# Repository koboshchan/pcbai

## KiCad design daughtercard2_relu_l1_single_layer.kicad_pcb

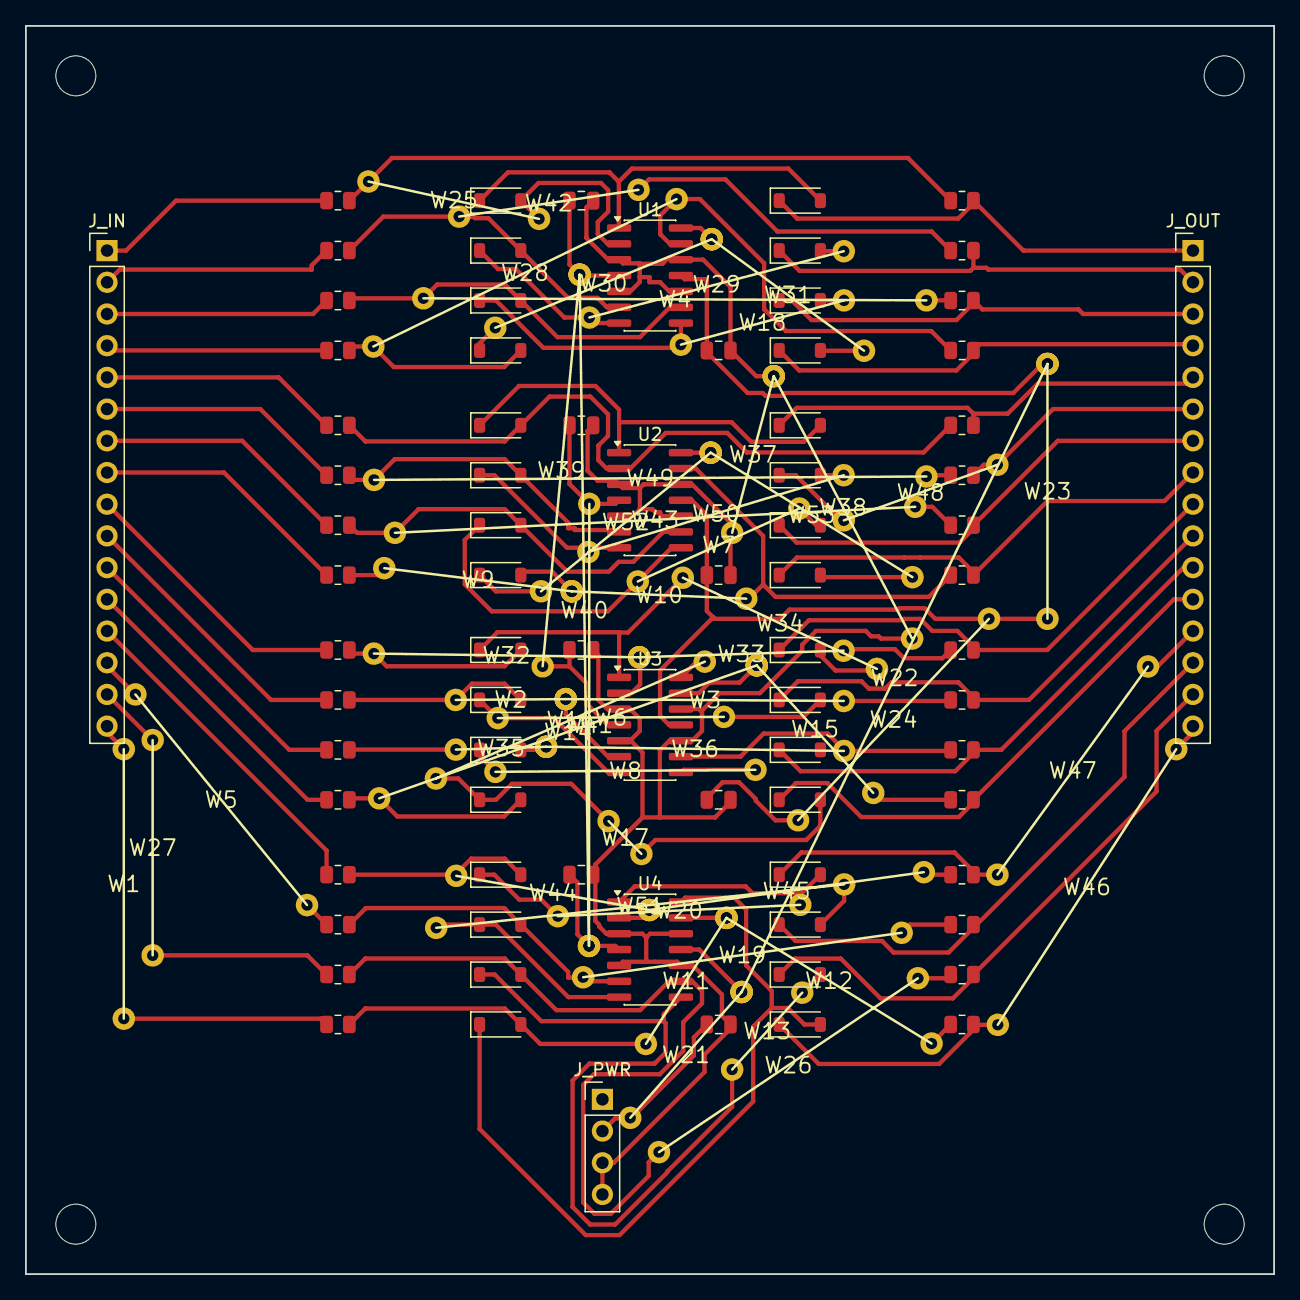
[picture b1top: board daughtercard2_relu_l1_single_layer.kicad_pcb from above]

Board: 2 copper layers, 100.0 x 100.0 mm, 136 parts (0 on the bottom side), 67 nets.

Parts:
C_1_NEG, C_1_POS, C_2_NEG, C_2_POS, C_3_NEG, C_3_POS, C_4_NEG, C_4_POS: 100n; C_0805_2012Metric
D_FB_0, D_FB_1, D_FB_2, D_FB_3, D_FB_4, D_FB_5, D_FB_6, D_FB_7, D_FB_8, D_FB_9, D_FB_10, D_FB_11, D_FB_12, D_FB_13, D_FB_14, D_FB_15: 1N4148; D_SOD-123
D_OUT_0, D_OUT_1, D_OUT_2, D_OUT_3, D_OUT_4, D_OUT_5, D_OUT_6, D_OUT_7, D_OUT_8, D_OUT_9, D_OUT_10, D_OUT_11, D_OUT_12, D_OUT_13, D_OUT_14, D_OUT_15: 1N4148; D_SOD-123
J_IN: V_SUM_IN; PinHeader_1x16_P2.54mm_Vertical
J_OUT: ACT_OUT; PinHeader_1x16_P2.54mm_Vertical
J_PWR: POWER; PinHeader_1x04_P2.54mm_Vertical
MH1, MH2, MH3, MH4: MountingHole_3.2mm_M3
R_FB_0, R_FB_1, R_FB_2, R_FB_3, R_FB_4, R_FB_5, R_FB_6, R_FB_7, R_FB_8, R_FB_9, R_FB_10, R_FB_11, R_FB_12, R_FB_13, R_FB_14, R_FB_15: 10k; R_0805_2012Metric
R_IN_0, R_IN_1, R_IN_2, R_IN_3, R_IN_4, R_IN_5, R_IN_6, R_IN_7, R_IN_8, R_IN_9, R_IN_10, R_IN_11, R_IN_12, R_IN_13, R_IN_14, R_IN_15: 10k; R_0805_2012Metric
U1, U2, U3, U4: TL074; SOIC-14_3.9x8.7mm_P1.27mm
W1, W2, W3, W4, W5, W6, W7, W8, W9, W10, W11, W12, W13, W14, W15, W16, W17, W18, W19, W20, W21, W22, W23, W24, W25, W26, W27, W28, W29, W30, W31, W32, W33, W34, W35, W36, W37, W38, W39, W40, W41, W42, W43, W44, W45, W46, W47, W48, W49, W50, W51, W52, W53: JUMPER; Jumper_Wire

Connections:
+12V: C_1_POS.1, C_2_POS.1, C_3_POS.1, C_4_POS.1, J_PWR.1, U1.4, U2.4, U3.4, U4.4, W39.1, W39.2, W40.1, W40.2, W41.1, W41.2
-12V: C_1_NEG.1, C_2_NEG.1, C_3_NEG.1, C_4_NEG.1, J_PWR.2, U1.11, U2.11, U3.11, U4.11, W21.1, W21.2, W22.1, W22.2, W23.1, W23.2, W24.1, W24.2
ACT_0: D_OUT_0.1, J_OUT.1, R_FB_0.2
ACT_1: D_OUT_1.1, J_OUT.2, R_FB_1.2
ACT_2: D_OUT_2.1, J_OUT.3, R_FB_2.2
ACT_3: D_OUT_3.1, J_OUT.4, R_FB_3.2
ACT_4: D_OUT_4.1, J_OUT.5, R_FB_4.2
ACT_5: D_OUT_5.1, J_OUT.6, R_FB_5.2, W48.1, W48.2
ACT_6: D_OUT_6.1, J_OUT.7, R_FB_6.2
ACT_7: D_OUT_7.1, J_OUT.8, R_FB_7.2
ACT_8: D_OUT_8.1, J_OUT.9, R_FB_8.2
ACT_9: D_OUT_9.1, J_OUT.10, R_FB_9.2
ACT_10: D_OUT_10.1, J_OUT.11, R_FB_10.2
ACT_11: D_OUT_11.1, J_OUT.12, R_FB_11.2
ACT_12: D_OUT_12.1, J_OUT.13, R_FB_12.2, W47.1, W47.2
ACT_13: D_OUT_13.1, J_OUT.14, R_FB_13.2
ACT_14: D_OUT_14.1, J_OUT.15, R_FB_14.2
ACT_15: D_OUT_15.1, J_OUT.16, R_FB_15.2, W46.1, W46.2
GND: C_1_NEG.2, C_1_POS.2, C_2_NEG.2, C_2_POS.2, C_3_NEG.2, C_3_POS.2, C_4_NEG.2, C_4_POS.2, J_PWR.3, J_PWR.4, U1.3, U1.5, U1.10, U1.12, U2.3, U2.5, U2.10, U2.12, U3.3, U3.5, U3.10, U3.12, U4.3, U4.5, U4.10, U4.12, W37.1, W37.2, W38.1, W38.2
INV_IN_0: D_FB_0.2, R_FB_0.1, R_IN_0.2, U1.2, W25.1, W25.2
INV_IN_1: D_FB_1.2, R_FB_1.1, R_IN_1.2, U1.6, W42.1, W42.2
INV_IN_2: D_FB_2.2, R_FB_2.1, R_IN_2.2, U1.9, W4.1, W4.2
INV_IN_3: D_FB_3.2, R_FB_3.1, R_IN_3.2, U1.13, W28.1, W28.2
INV_IN_4: D_FB_4.2, R_FB_4.1, R_IN_4.2, U2.2
INV_IN_5: D_FB_5.2, R_FB_5.1, R_IN_5.2, U2.6, W49.1, W49.2
INV_IN_6: D_FB_6.2, R_FB_6.1, R_IN_6.2, U2.9, W43.1, W43.2
INV_IN_7: D_FB_7.2, R_FB_7.1, R_IN_7.2, U2.13, W9.1, W9.2, W10.1, W10.2
INV_IN_8: D_FB_8.2, R_FB_8.1, R_IN_8.2, U3.2, W32.1, W32.2, W33.1, W33.2
INV_IN_9: D_FB_9.2, R_FB_9.1, R_IN_9.2, U3.6, W2.1, W2.2, W3.1, W3.2
INV_IN_10: D_FB_10.2, R_FB_10.1, R_IN_10.2, U3.9, W35.1, W35.2, W36.1, W36.2
INV_IN_11: D_FB_11.2, R_FB_11.1, R_IN_11.2, U3.13, W14.1, W14.2, W15.1, W15.2
INV_IN_12: D_FB_12.2, R_FB_12.1, R_IN_12.2, U4.2, W44.1, W44.2, W45.1, W45.2
INV_IN_13: D_FB_13.2, R_FB_13.1, R_IN_13.2, U4.6, W19.1, W19.2
INV_IN_14: D_FB_14.2, R_FB_14.1, R_IN_14.2, U4.9, W26.1, W26.2
INV_IN_15: D_FB_15.2, R_FB_15.1, R_IN_15.2, U4.13, W11.1, W11.2, W12.1, W12.2
OP_OUT_0: D_FB_0.1, D_OUT_0.2, U1.1
OP_OUT_1: D_FB_1.1, D_OUT_1.2, U1.7, W29.1, W29.2
OP_OUT_2: D_FB_2.1, D_OUT_2.2, U1.8, W18.1, W18.2
OP_OUT_3: D_FB_3.1, D_OUT_3.2, U1.14, W30.1, W30.2, W31.1, W31.2
OP_OUT_4: D_FB_4.1, D_OUT_4.2, U2.1
OP_OUT_5: D_FB_5.1, D_OUT_5.2, U2.7, W50.1, W50.2
OP_OUT_6: D_FB_6.1, D_OUT_6.2, U2.8, W7.1, W7.2
OP_OUT_7: D_FB_7.1, D_OUT_7.2, U2.14, W52.1, W52.2, W53.1, W53.2
OP_OUT_8: D_FB_8.1, D_OUT_8.2, U3.1, W34.1, W34.2
OP_OUT_9: D_FB_9.1, D_OUT_9.2, U3.7, W6.1, W6.2
OP_OUT_10: D_FB_10.1, D_OUT_10.2, U3.8, W8.1, W8.2
OP_OUT_11: D_FB_11.1, D_OUT_11.2, U3.14, W16.1, W16.2, W17.1, W17.2
OP_OUT_12: D_FB_12.1, D_OUT_12.2, U4.1, W20.1, W20.2
OP_OUT_13: D_FB_13.1, D_OUT_13.2, U4.7, W51.1, W51.2
OP_OUT_14: D_FB_14.1, D_OUT_14.2, U4.8, W13.1, W13.2
OP_OUT_15: D_FB_15.1, D_OUT_15.2, U4.14
V_SUM_0: J_IN.1, R_IN_0.1
V_SUM_1: J_IN.2, R_IN_1.1
V_SUM_2: J_IN.3, R_IN_2.1
V_SUM_3: J_IN.4, R_IN_3.1
V_SUM_4: J_IN.5, R_IN_4.1
V_SUM_5: J_IN.6, R_IN_5.1
V_SUM_6: J_IN.7, R_IN_6.1
V_SUM_7: J_IN.8, R_IN_7.1
V_SUM_8: J_IN.9, R_IN_8.1
V_SUM_9: J_IN.10, R_IN_9.1
V_SUM_10: J_IN.11, R_IN_10.1
V_SUM_11: J_IN.12, R_IN_11.1
V_SUM_12: J_IN.13, R_IN_12.1
V_SUM_13: J_IN.14, R_IN_13.1, W5.1, W5.2
V_SUM_14: J_IN.15, R_IN_14.1, W27.1, W27.2
V_SUM_15: J_IN.16, R_IN_15.1, W1.1, W1.2

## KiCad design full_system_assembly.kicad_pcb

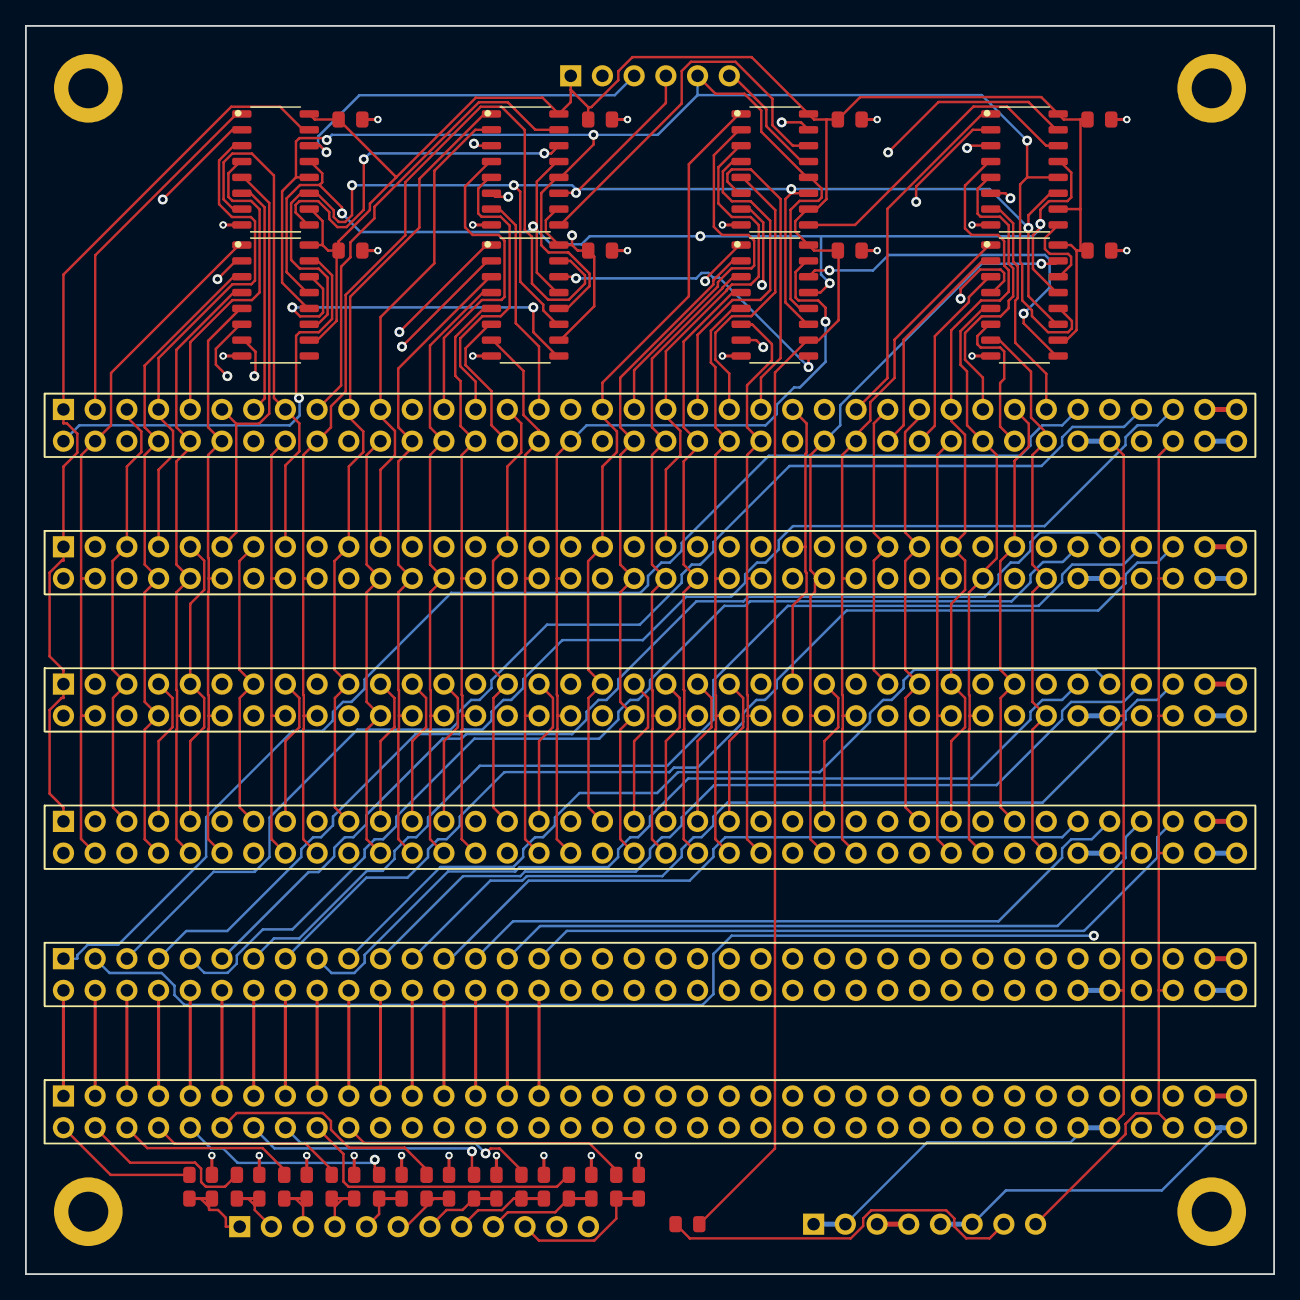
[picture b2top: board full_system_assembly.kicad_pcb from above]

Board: 4 copper layers, 100.0 x 100.0 mm, 50 parts (0 on the bottom side), 133 nets.

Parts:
C_SR1, C_SR2, C_SR3, C_SR4, C_SR5, C_SR6, C_SR7, C_SR8: 0.1uF; C_0805_2012Metric
H1, H2, H3, H4: MountingHole; MountingHole_3.2mm_M3_Pad
J_MCU_SCORES: Scores_DIV_3V3_Out; PinHeader_1x12_P2.54mm_Vertical
J_MCU_SPI: MCU_SPI_In; PinHeader_1x06_P2.54mm_Vertical
J_PWR_IN: Main_Power_In; PinHeader_1x08_P2.54mm_Vertical
J_SLOT0: Slot0: DC1A (L1 Neurons 0..3); PinSocket_2x38_P2.54mm_Vertical
J_SLOT1: Slot1: DC1B (L1 Neurons 4..7); PinSocket_2x38_P2.54mm_Vertical
J_SLOT2: Slot2: DC1C (L1 Neurons 8..11); PinSocket_2x38_P2.54mm_Vertical
J_SLOT3: Slot3: DC1D (L1 Neurons 12..15); PinSocket_2x38_P2.54mm_Vertical
J_SLOT4: Slot4: DC2 (16x Active Precision ReLU); PinSocket_2x38_P2.54mm_Vertical
J_SLOT5: Slot5: DC3 (L2 Weights + 10-Way WTA); PinSocket_2x38_P2.54mm_Vertical
R_BOT_0, R_BOT_1, R_BOT_2, R_BOT_3, R_BOT_4, R_BOT_5, R_BOT_6, R_BOT_7, R_BOT_8, R_BOT_9: 20k; R_0805_2012Metric
R_PWR5: 0R; R_0805_2012Metric
R_TOP_0, R_TOP_1, R_TOP_2, R_TOP_3, R_TOP_4, R_TOP_5, R_TOP_6, R_TOP_7, R_TOP_8, R_TOP_9: 10k; R_0805_2012Metric
U_SR1, U_SR2, U_SR3, U_SR4, U_SR5, U_SR6, U_SR7, U_SR8: 74HC595D; SOIC-16_3.9x9.9mm_P1.27mm

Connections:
+5V: C_SR1.1, C_SR2.1, C_SR3.1, C_SR4.1, C_SR5.1, C_SR6.1, C_SR7.1, C_SR8.1, J_MCU_SPI.1, R_PWR5.2, U_SR1.10, U_SR1.16, U_SR2.10, U_SR2.16, U_SR3.10, U_SR3.16, U_SR4.10, U_SR4.16, U_SR5.10, U_SR5.16, U_SR6.10, U_SR6.16, U_SR7.10, U_SR7.16, U_SR8.10, U_SR8.16
+5V_REF: J_PWR_IN.7, J_SLOT0.B35, J_SLOT1.B35, J_SLOT2.B35, J_SLOT3.B35, J_SLOT4.B35, J_SLOT5.B35, R_PWR5.1
+12V: J_PWR_IN.1, J_PWR_IN.2, J_SLOT0.B33, J_SLOT0.B34, J_SLOT1.B33, J_SLOT1.B34, J_SLOT2.B33, J_SLOT2.B34, J_SLOT3.B33, J_SLOT3.B34, J_SLOT4.B33, J_SLOT4.B34, J_SLOT5.B33, J_SLOT5.B34
-5V_REF: J_PWR_IN.8, J_SLOT0.B36, J_SLOT1.B36, J_SLOT2.B36, J_SLOT3.B36, J_SLOT4.B36, J_SLOT5.B36
-12V: J_PWR_IN.5, J_PWR_IN.6, J_SLOT0.B37, J_SLOT0.B38, J_SLOT1.B37, J_SLOT1.B38, J_SLOT2.B37, J_SLOT2.B38, J_SLOT3.B37, J_SLOT3.B38, J_SLOT4.B37, J_SLOT4.B38, J_SLOT5.B37, J_SLOT5.B38
ACT_0: J_SLOT4.B1, J_SLOT5.A1
ACT_1: J_SLOT4.B2, J_SLOT5.A2
ACT_2: J_SLOT4.B3, J_SLOT5.A3
ACT_3: J_SLOT4.B4, J_SLOT5.A4
ACT_4: J_SLOT4.B5, J_SLOT5.A5
ACT_5: J_SLOT4.B6, J_SLOT5.A6
ACT_6: J_SLOT4.B7, J_SLOT5.A7
ACT_7: J_SLOT4.B8, J_SLOT5.A8
ACT_8: J_SLOT4.B9, J_SLOT5.A9
ACT_9: J_SLOT4.B10, J_SLOT5.A10
ACT_10: J_SLOT4.B11, J_SLOT5.A11
ACT_11: J_SLOT4.B12, J_SLOT5.A12
ACT_12: J_SLOT4.B13, J_SLOT5.A13
ACT_13: J_SLOT4.B14, J_SLOT5.A14
ACT_14: J_SLOT4.B15, J_SLOT5.A15
ACT_15: J_SLOT4.B16, J_SLOT5.A16
GND: C_SR1.2, C_SR2.2, C_SR3.2, C_SR4.2, C_SR5.2, C_SR6.2, C_SR7.2, C_SR8.2, H1.1, H2.1, H3.1, H4.1, J_MCU_SCORES.11, J_MCU_SCORES.12, J_MCU_SPI.2, J_PWR_IN.3, J_PWR_IN.4, J_SLOT0.A37, J_SLOT0.A38, J_SLOT1.A37, J_SLOT1.A38, J_SLOT2.A37, J_SLOT2.A38, J_SLOT3.A37, J_SLOT3.A38, J_SLOT4.A17, J_SLOT4.A18, J_SLOT4.A19, J_SLOT4.A20, J_SLOT4.A21, J_SLOT4.A22, J_SLOT4.A23, J_SLOT4.A24, J_SLOT4.A25, J_SLOT4.A26, J_SLOT4.A27, J_SLOT4.A28, J_SLOT4.A29, J_SLOT4.A30, J_SLOT4.A31, J_SLOT4.A32, J_SLOT4.A33, J_SLOT4.A34, J_SLOT4.A35, J_SLOT4.A36, J_SLOT4.A37, J_SLOT4.A38, J_SLOT4.B17, J_SLOT4.B18, J_SLOT4.B19, J_SLOT4.B20, J_SLOT4.B21, J_SLOT4.B22, J_SLOT4.B23, J_SLOT4.B24, J_SLOT4.B25, J_SLOT4.B26, J_SLOT4.B27, J_SLOT4.B28, J_SLOT4.B29, J_SLOT4.B30, J_SLOT4.B31, J_SLOT4.B32, J_SLOT5.A17, J_SLOT5.A18, J_SLOT5.A19, J_SLOT5.A20, J_SLOT5.A21, J_SLOT5.A22, J_SLOT5.A23, J_SLOT5.A24, J_SLOT5.A25, J_SLOT5.A26, J_SLOT5.A27, J_SLOT5.A28, J_SLOT5.A29, J_SLOT5.A30, J_SLOT5.A31, J_SLOT5.A32, J_SLOT5.A33, J_SLOT5.A34, J_SLOT5.A35, J_SLOT5.A36, J_SLOT5.A37, J_SLOT5.A38, J_SLOT5.B11, J_SLOT5.B12, J_SLOT5.B13, J_SLOT5.B14, J_SLOT5.B15, J_SLOT5.B16, J_SLOT5.B17, J_SLOT5.B18, J_SLOT5.B19, J_SLOT5.B20, J_SLOT5.B21, J_SLOT5.B22, J_SLOT5.B23, J_SLOT5.B24, J_SLOT5.B25, J_SLOT5.B26, J_SLOT5.B27, J_SLOT5.B28, J_SLOT5.B29, J_SLOT5.B30, J_SLOT5.B31, J_SLOT5.B32, R_BOT_0.1, R_BOT_1.1, R_BOT_2.1, R_BOT_3.1, R_BOT_4.1, R_BOT_5.1, R_BOT_6.1, R_BOT_7.1, R_BOT_8.1, R_BOT_9.1, U_SR1.8, U_SR2.8, U_SR3.8, U_SR4.8, U_SR5.8, U_SR6.8, U_SR7.8, U_SR8.8
IN_0: J_SLOT0.A1, J_SLOT1.A1, J_SLOT2.A1, J_SLOT3.A1, U_SR1.15
IN_1: J_SLOT0.A2, J_SLOT1.A2, J_SLOT2.A2, J_SLOT3.A2, U_SR1.1
IN_2: J_SLOT0.A3, J_SLOT1.A3, J_SLOT2.A3, J_SLOT3.A3, U_SR1.2
IN_3: J_SLOT0.A4, J_SLOT1.A4, J_SLOT2.A4, J_SLOT3.A4, U_SR1.3
IN_4: J_SLOT0.A5, J_SLOT1.A5, J_SLOT2.A5, J_SLOT3.A5, U_SR1.4
IN_5: J_SLOT0.A6, J_SLOT1.A6, J_SLOT2.A6, J_SLOT3.A6, U_SR1.5
IN_6: J_SLOT0.A7, J_SLOT1.A7, J_SLOT2.A7, J_SLOT3.A7, U_SR1.6
IN_7: J_SLOT0.A8, J_SLOT1.A8, J_SLOT2.A8, J_SLOT3.A8, U_SR1.7
IN_8: J_SLOT0.A9, J_SLOT1.A9, J_SLOT2.A9, J_SLOT3.A9, U_SR2.15
IN_9: J_SLOT0.A10, J_SLOT1.A10, J_SLOT2.A10, J_SLOT3.A10, U_SR2.1
IN_10: J_SLOT0.A11, J_SLOT1.A11, J_SLOT2.A11, J_SLOT3.A11, U_SR2.2
IN_11: J_SLOT0.A12, J_SLOT1.A12, J_SLOT2.A12, J_SLOT3.A12, U_SR2.3
IN_12: J_SLOT0.A13, J_SLOT1.A13, J_SLOT2.A13, J_SLOT3.A13, U_SR2.4
IN_13: J_SLOT0.A14, J_SLOT1.A14, J_SLOT2.A14, J_SLOT3.A14, U_SR2.5
IN_14: J_SLOT0.A15, J_SLOT1.A15, J_SLOT2.A15, J_SLOT3.A15, U_SR2.6
IN_15: J_SLOT0.A16, J_SLOT1.A16, J_SLOT2.A16, J_SLOT3.A16, U_SR2.7
IN_16: J_SLOT0.A17, J_SLOT1.A17, J_SLOT2.A17, J_SLOT3.A17, U_SR3.15
IN_17: J_SLOT0.A18, J_SLOT1.A18, J_SLOT2.A18, J_SLOT3.A18, U_SR3.1
IN_18: J_SLOT0.A19, J_SLOT1.A19, J_SLOT2.A19, J_SLOT3.A19, U_SR3.2
IN_19: J_SLOT0.A20, J_SLOT1.A20, J_SLOT2.A20, J_SLOT3.A20, U_SR3.3
IN_20: J_SLOT0.A21, J_SLOT1.A21, J_SLOT2.A21, J_SLOT3.A21, U_SR3.4
IN_21: J_SLOT0.A22, J_SLOT1.A22, J_SLOT2.A22, J_SLOT3.A22, U_SR3.5
IN_22: J_SLOT0.A23, J_SLOT1.A23, J_SLOT2.A23, J_SLOT3.A23, U_SR3.6
IN_23: J_SLOT0.A24, J_SLOT1.A24, J_SLOT2.A24, J_SLOT3.A24, U_SR3.7
IN_24: J_SLOT0.A25, J_SLOT1.A25, J_SLOT2.A25, J_SLOT3.A25, U_SR4.15
IN_25: J_SLOT0.A26, J_SLOT1.A26, J_SLOT2.A26, J_SLOT3.A26, U_SR4.1
IN_26: J_SLOT0.A27, J_SLOT1.A27, J_SLOT2.A27, J_SLOT3.A27, U_SR4.2
IN_27: J_SLOT0.A28, J_SLOT1.A28, J_SLOT2.A28, J_SLOT3.A28, U_SR4.3
IN_28: J_SLOT0.A29, J_SLOT1.A29, J_SLOT2.A29, J_SLOT3.A29, U_SR4.4
IN_29: J_SLOT0.A30, J_SLOT1.A30, J_SLOT2.A30, J_SLOT3.A30, U_SR4.5
IN_30: J_SLOT0.A31, J_SLOT1.A31, J_SLOT2.A31, J_SLOT3.A31, U_SR4.6
IN_31: J_SLOT0.A32, J_SLOT1.A32, J_SLOT2.A32, J_SLOT3.A32, U_SR4.7
IN_32: J_SLOT0.B1, J_SLOT1.B1, J_SLOT2.B1, J_SLOT3.B1, U_SR8.15
IN_33: J_SLOT0.B2, J_SLOT1.B2, J_SLOT2.B2, J_SLOT3.B2, U_SR8.1
IN_34: J_SLOT0.B3, J_SLOT1.B3, J_SLOT2.B3, J_SLOT3.B3, U_SR8.2
IN_35: J_SLOT0.B4, J_SLOT1.B4, J_SLOT2.B4, J_SLOT3.B4, U_SR8.3
IN_36: J_SLOT0.B5, J_SLOT1.B5, J_SLOT2.B5, J_SLOT3.B5, U_SR8.4
IN_37: J_SLOT0.B6, J_SLOT1.B6, J_SLOT2.B6, J_SLOT3.B6, U_SR8.5
IN_38: J_SLOT0.B7, J_SLOT1.B7, J_SLOT2.B7, J_SLOT3.B7, U_SR8.6
IN_39: J_SLOT0.B8, J_SLOT1.B8, J_SLOT2.B8, J_SLOT3.B8, U_SR8.7
IN_40: J_SLOT0.B9, J_SLOT1.B9, J_SLOT2.B9, J_SLOT3.B9, U_SR7.15
IN_41: J_SLOT0.B10, J_SLOT1.B10, J_SLOT2.B10, J_SLOT3.B10, U_SR7.1
IN_42: J_SLOT0.B11, J_SLOT1.B11, J_SLOT2.B11, J_SLOT3.B11, U_SR7.2
IN_43: J_SLOT0.B12, J_SLOT1.B12, J_SLOT2.B12, J_SLOT3.B12, U_SR7.3
IN_44: J_SLOT0.B13, J_SLOT1.B13, J_SLOT2.B13, J_SLOT3.B13, U_SR7.4
IN_45: J_SLOT0.B14, J_SLOT1.B14, J_SLOT2.B14, J_SLOT3.B14, U_SR7.5
IN_46: J_SLOT0.B15, J_SLOT1.B15, J_SLOT2.B15, J_SLOT3.B15, U_SR7.6
IN_47: J_SLOT0.B16, J_SLOT1.B16, J_SLOT2.B16, J_SLOT3.B16, U_SR7.7
IN_48: J_SLOT0.B17, J_SLOT1.B17, J_SLOT2.B17, J_SLOT3.B17, U_SR6.15
IN_49: J_SLOT0.B18, J_SLOT1.B18, J_SLOT2.B18, J_SLOT3.B18, U_SR6.1
IN_50: J_SLOT0.B19, J_SLOT1.B19, J_SLOT2.B19, J_SLOT3.B19, U_SR6.2
IN_51: J_SLOT0.B20, J_SLOT1.B20, J_SLOT2.B20, J_SLOT3.B20, U_SR6.3
IN_52: J_SLOT0.B21, J_SLOT1.B21, J_SLOT2.B21, J_SLOT3.B21, U_SR6.4
IN_53: J_SLOT0.B22, J_SLOT1.B22, J_SLOT2.B22, J_SLOT3.B22, U_SR6.5
IN_54: J_SLOT0.B23, J_SLOT1.B23, J_SLOT2.B23, J_SLOT3.B23, U_SR6.6
IN_55: J_SLOT0.B24, J_SLOT1.B24, J_SLOT2.B24, J_SLOT3.B24, U_SR6.7
IN_56: J_SLOT0.B25, J_SLOT1.B25, J_SLOT2.B25, J_SLOT3.B25, U_SR5.15
IN_57: J_SLOT0.B26, J_SLOT1.B26, J_SLOT2.B26, J_SLOT3.B26, U_SR5.1
IN_58: J_SLOT0.B27, J_SLOT1.B27, J_SLOT2.B27, J_SLOT3.B27, U_SR5.2
IN_59: J_SLOT0.B28, J_SLOT1.B28, J_SLOT2.B28, J_SLOT3.B28, U_SR5.3
IN_60: J_SLOT0.B29, J_SLOT1.B29, J_SLOT2.B29, J_SLOT3.B29, U_SR5.4
IN_61: J_SLOT0.B30, J_SLOT1.B30, J_SLOT2.B30, J_SLOT3.B30, U_SR5.5
IN_62: J_SLOT0.B31, J_SLOT1.B31, J_SLOT2.B31, J_SLOT3.B31, U_SR5.6
IN_63: J_SLOT0.B32, J_SLOT1.B32, J_SLOT2.B32, J_SLOT3.B32, U_SR5.7
SCORE_0: J_SLOT5.B1, R_TOP_0.1
SCORE_1: J_SLOT5.B2, R_TOP_1.1
SCORE_2: J_SLOT5.B3, R_TOP_2.1
SCORE_3: J_SLOT5.B4, R_TOP_3.1
SCORE_4: J_SLOT5.B5, R_TOP_4.1
SCORE_5: J_SLOT5.B6, R_TOP_5.1
SCORE_6: J_SLOT5.B7, R_TOP_6.1
SCORE_7: J_SLOT5.B8, R_TOP_7.1
SCORE_8: J_SLOT5.B9, R_TOP_8.1
SCORE_9: J_SLOT5.B10, R_TOP_9.1
SCORE_DIV_0: J_MCU_SCORES.1, R_BOT_0.2, R_TOP_0.2
SCORE_DIV_1: J_MCU_SCORES.2, R_BOT_1.2, R_TOP_1.2
SCORE_DIV_2: J_MCU_SCORES.3, R_BOT_2.2, R_TOP_2.2
SCORE_DIV_3: J_MCU_SCORES.4, R_BOT_3.2, R_TOP_3.2
SCORE_DIV_4: J_MCU_SCORES.5, R_BOT_4.2, R_TOP_4.2
SCORE_DIV_5: J_MCU_SCORES.6, R_BOT_5.2, R_TOP_5.2
SCORE_DIV_6: J_MCU_SCORES.7, R_BOT_6.2, R_TOP_6.2
SCORE_DIV_7: J_MCU_SCORES.8, R_BOT_7.2, R_TOP_7.2
SCORE_DIV_8: J_MCU_SCORES.9, R_BOT_8.2, R_TOP_8.2
SCORE_DIV_9: J_MCU_SCORES.10, R_BOT_9.2, R_TOP_9.2
SPI_LATCH: J_MCU_SPI.5, U_SR1.12, U_SR2.12, U_SR3.12, U_SR4.12, U_SR5.12, U_SR6.12, U_SR7.12, U_SR8.12
SPI_MOSI: J_MCU_SPI.3, U_SR1.14
SPI_OE: J_MCU_SPI.6, U_SR1.13, U_SR2.13, U_SR3.13, U_SR4.13, U_SR5.13, U_SR6.13, U_SR7.13, U_SR8.13
SPI_SCK: J_MCU_SPI.4, U_SR1.11, U_SR2.11, U_SR3.11, U_SR4.11, U_SR5.11, U_SR6.11, U_SR7.11, U_SR8.11
SR_CHAIN_1: U_SR1.9, U_SR2.14
SR_CHAIN_2: U_SR2.9, U_SR3.14
SR_CHAIN_3: U_SR3.9, U_SR4.14
SR_CHAIN_4: U_SR4.9, U_SR5.14
SR_CHAIN_5: U_SR5.9, U_SR6.14
SR_CHAIN_6: U_SR6.9, U_SR7.14
SR_CHAIN_7: U_SR7.9, U_SR8.14
V_SUM_0: J_SLOT0.A33, J_SLOT4.A1
V_SUM_1: J_SLOT0.A34, J_SLOT4.A2
V_SUM_2: J_SLOT0.A35, J_SLOT4.A3
V_SUM_3: J_SLOT0.A36, J_SLOT4.A4
V_SUM_4: J_SLOT1.A33, J_SLOT4.A5
V_SUM_5: J_SLOT1.A34, J_SLOT4.A6
V_SUM_6: J_SLOT1.A35, J_SLOT4.A7
V_SUM_7: J_SLOT1.A36, J_SLOT4.A8
V_SUM_8: J_SLOT2.A33, J_SLOT4.A9
V_SUM_9: J_SLOT2.A34, J_SLOT4.A10
V_SUM_10: J_SLOT2.A35, J_SLOT4.A11
V_SUM_11: J_SLOT2.A36, J_SLOT4.A12
V_SUM_12: J_SLOT3.A33, J_SLOT4.A13
V_SUM_13: J_SLOT3.A34, J_SLOT4.A14
V_SUM_14: J_SLOT3.A35, J_SLOT4.A15
V_SUM_15: J_SLOT3.A36, J_SLOT4.A16

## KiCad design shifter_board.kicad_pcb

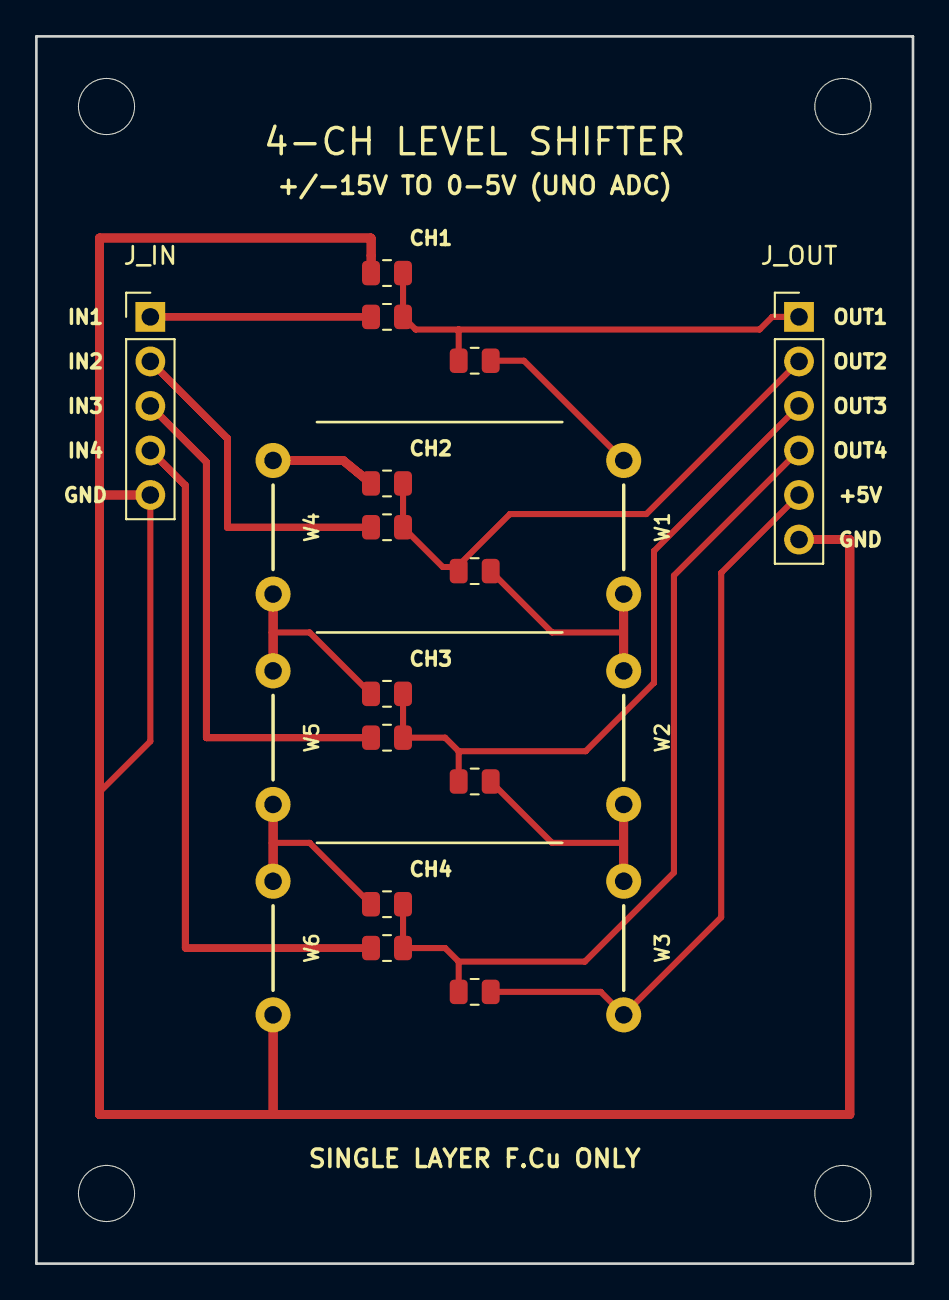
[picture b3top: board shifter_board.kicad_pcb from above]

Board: 2 copper layers, 50.0 x 70.0 mm, 24 parts (0 on the bottom side), 16 nets.

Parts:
J_IN: 1x05_IN_GND; PinHeader_1x05_P2.54mm_Vertical
J_OUT: 1x06_OUT_5V_GND; PinHeader_1x06_P2.54mm_Vertical
MH1, MH2, MH3, MH4: MountingHole_3.2mm_M3
R1_PD, R1_PU, R2_PD, R2_PU, R3_PD, R3_PU, R4_PD, R4_PU: 10k; R_0805_2012Metric
R1_TOP, R2_TOP, R3_TOP, R4_TOP: 33k; R_0805_2012Metric
W1, W2, W3, W4, W5, W6: Jumper_Wire

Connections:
+5V: J_OUT.5, R4_PU.2, W3.2
+5V_CH1: R1_PU.2, W1.1
+5V_CH2: R2_PU.2, W1.2, W2.1
+5V_CH3: R3_PU.2, W2.2, W3.1
GND: J_IN.5, J_OUT.6, R1_PD.1, W6.2
GND_CH1: R2_PD.1, W4.1
GND_CH2: R3_PD.1, W4.2, W5.1
GND_CH3: R4_PD.1, W5.2, W6.1
IN1: J_IN.1, R1_TOP.1
IN2: J_IN.2, R2_TOP.1
IN3: J_IN.3, R3_TOP.1
IN4: J_IN.4, R4_TOP.1
MID1: J_OUT.1, R1_PD.2, R1_PU.1, R1_TOP.2
MID2: J_OUT.2, R2_PD.2, R2_PU.1, R2_TOP.2
MID3: J_OUT.3, R3_PD.2, R3_PU.1, R3_TOP.2
MID4: J_OUT.4, R4_PD.2, R4_PU.1, R4_TOP.2

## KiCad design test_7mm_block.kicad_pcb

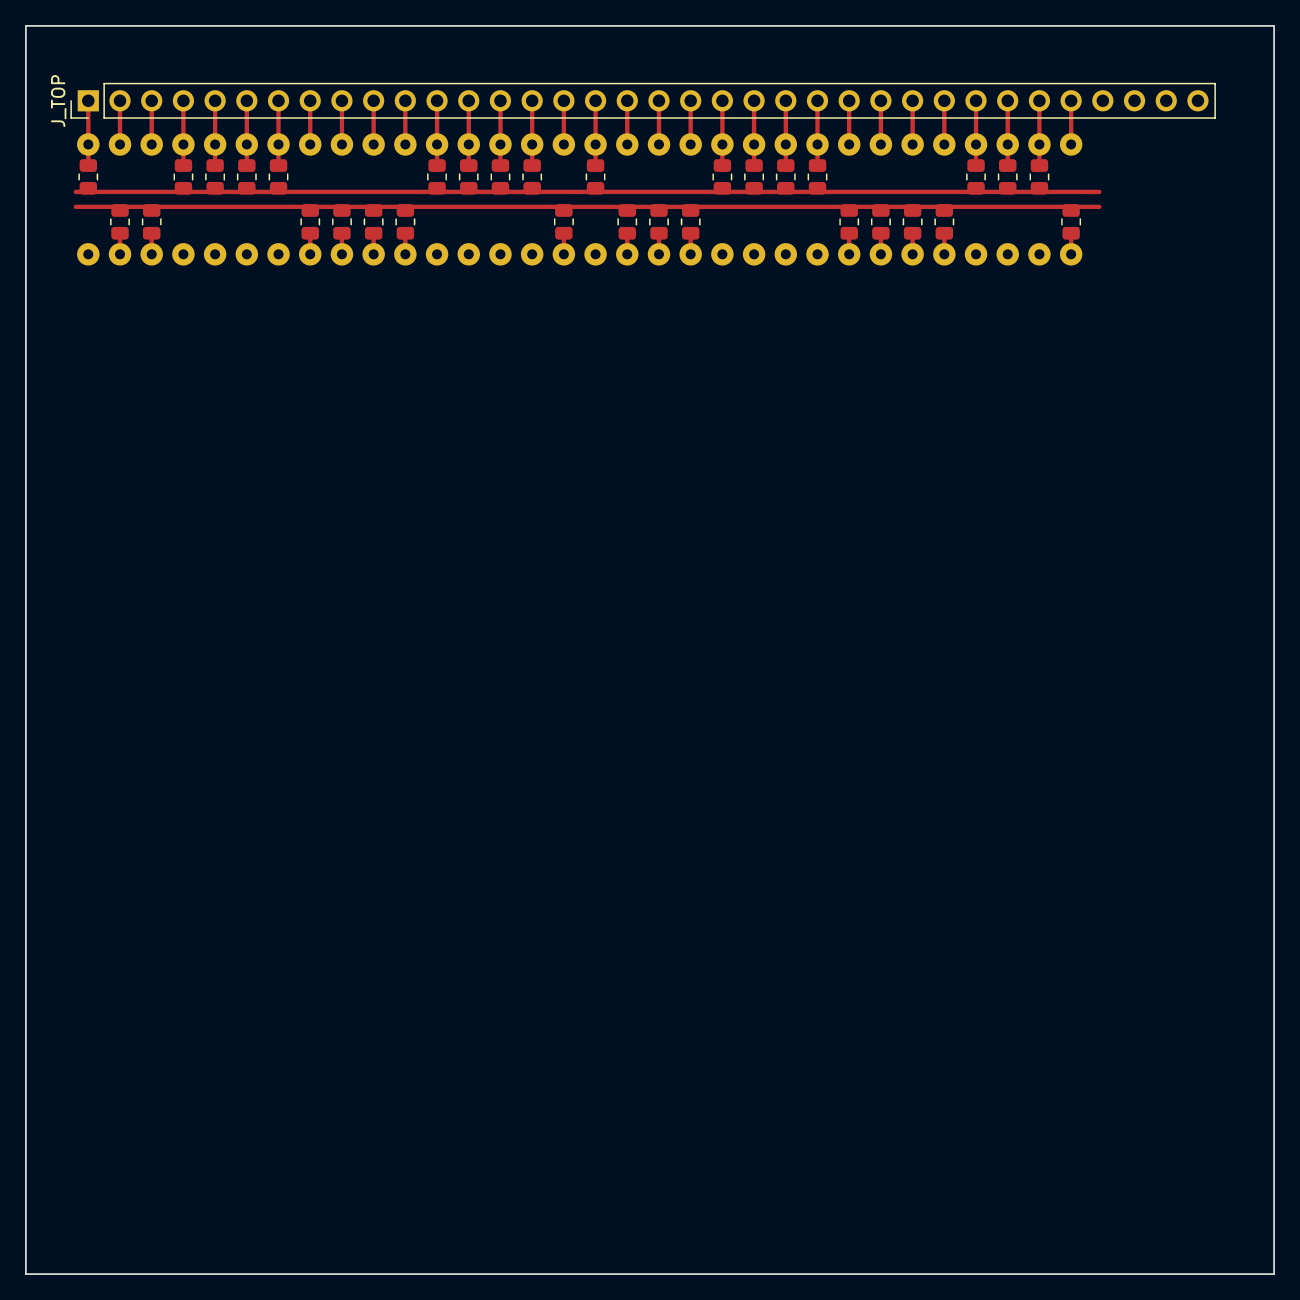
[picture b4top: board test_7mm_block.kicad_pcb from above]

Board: 2 copper layers, 100.0 x 100.0 mm, 65 parts (0 on the bottom side), 34 nets.

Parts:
J_TOP: INPUTS_0_31_PWR; PinHeader_1x36_P2.54mm_Vertical
R1_0_0, R1_4_0, R1_7_0, R1_21_0, R1_22_0, R1_27_0: 12k; R_0805_2012Metric
R1_1_0, R1_10_0, R1_28_0: 200k; R_0805_2012Metric
R1_2_0, R1_8_0, R1_16_0, R1_24_0, R1_29_0: 22k; R_0805_2012Metric
R1_3_0: 100k; R_0805_2012Metric
R1_5_0, R1_9_0, R1_13_0, R1_14_0, R1_25_0, R1_26_0: 33k; R_0805_2012Metric
R1_6_0, R1_11_0, R1_17_0: 75k; R_0805_2012Metric
R1_12_0: 18k; R_0805_2012Metric
R1_15_0: 300k; R_0805_2012Metric
R1_18_0: 43k; R_0805_2012Metric
R1_19_0: 10k; R_0805_2012Metric
R1_20_0: 51k; R_0805_2012Metric
R1_23_0: 15k; R_0805_2012Metric
R1_30_0: 20k; R_0805_2012Metric
R1_31_0: 390k; R_0805_2012Metric
W1, W2, W3, W4, W5, W6, W7, W8, W9, W10, W11, W12, W13, W14, W15, W16, W17, W18, W19, W20, W21, W22, W23, W24, W25, W26, W27, W28, W29, W30, W31, W32: JUMPER; Jumper_Wire

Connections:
IN_0: J_TOP.1, R1_0_0.1, W1.1
IN_1: J_TOP.2, R1_1_0.1, W2.1
IN_2: J_TOP.3, R1_2_0.1, W3.1
IN_3: J_TOP.4, R1_3_0.1, W4.1
IN_4: J_TOP.5, R1_4_0.1, W5.1
IN_5: J_TOP.6, R1_5_0.1, W6.1
IN_6: J_TOP.7, R1_6_0.1, W7.1
IN_7: J_TOP.8, R1_7_0.1, W8.1
IN_8: J_TOP.9, R1_8_0.1, W9.1
IN_9: J_TOP.10, R1_9_0.1, W10.1
IN_10: J_TOP.11, R1_10_0.1, W11.1
IN_11: J_TOP.12, R1_11_0.1, W12.1
IN_12: J_TOP.13, R1_12_0.1, W13.1
IN_13: J_TOP.14, R1_13_0.1, W14.1
IN_14: J_TOP.15, R1_14_0.1, W15.1
IN_15: J_TOP.16, R1_15_0.1, W16.1
IN_16: J_TOP.17, R1_16_0.1, W17.1
IN_17: J_TOP.18, R1_17_0.1, W18.1
IN_18: J_TOP.19, R1_18_0.1, W19.1
IN_19: J_TOP.20, R1_19_0.1, W20.1
IN_20: J_TOP.21, R1_20_0.1, W21.1
IN_21: J_TOP.22, R1_21_0.1, W22.1
IN_22: J_TOP.23, R1_22_0.1, W23.1
IN_23: J_TOP.24, R1_23_0.1, W24.1
IN_24: J_TOP.25, R1_24_0.1, W25.1
IN_25: J_TOP.26, R1_25_0.1, W26.1
IN_26: J_TOP.27, R1_26_0.1, W27.1
IN_27: J_TOP.28, R1_27_0.1, W28.1
IN_28: J_TOP.29, R1_28_0.1, W29.1
IN_29: J_TOP.30, R1_29_0.1, W30.1
IN_30: J_TOP.31, R1_30_0.1, W31.1
IN_31: J_TOP.32, R1_31_0.1, W32.1
SUM_NEG_0: R1_1_0.2, R1_2_0.2, R1_7_0.2, R1_8_0.2, R1_9_0.2, R1_10_0.2, R1_15_0.2, R1_17_0.2, R1_18_0.2, R1_19_0.2, R1_24_0.2, R1_25_0.2, R1_26_0.2, R1_27_0.2, R1_31_0.2
SUM_POS_0: R1_0_0.2, R1_3_0.2, R1_4_0.2, R1_5_0.2, R1_6_0.2, R1_11_0.2, R1_12_0.2, R1_13_0.2, R1_14_0.2, R1_16_0.2, R1_20_0.2, R1_21_0.2, R1_22_0.2, R1_23_0.2, R1_28_0.2, R1_29_0.2, R1_30_0.2

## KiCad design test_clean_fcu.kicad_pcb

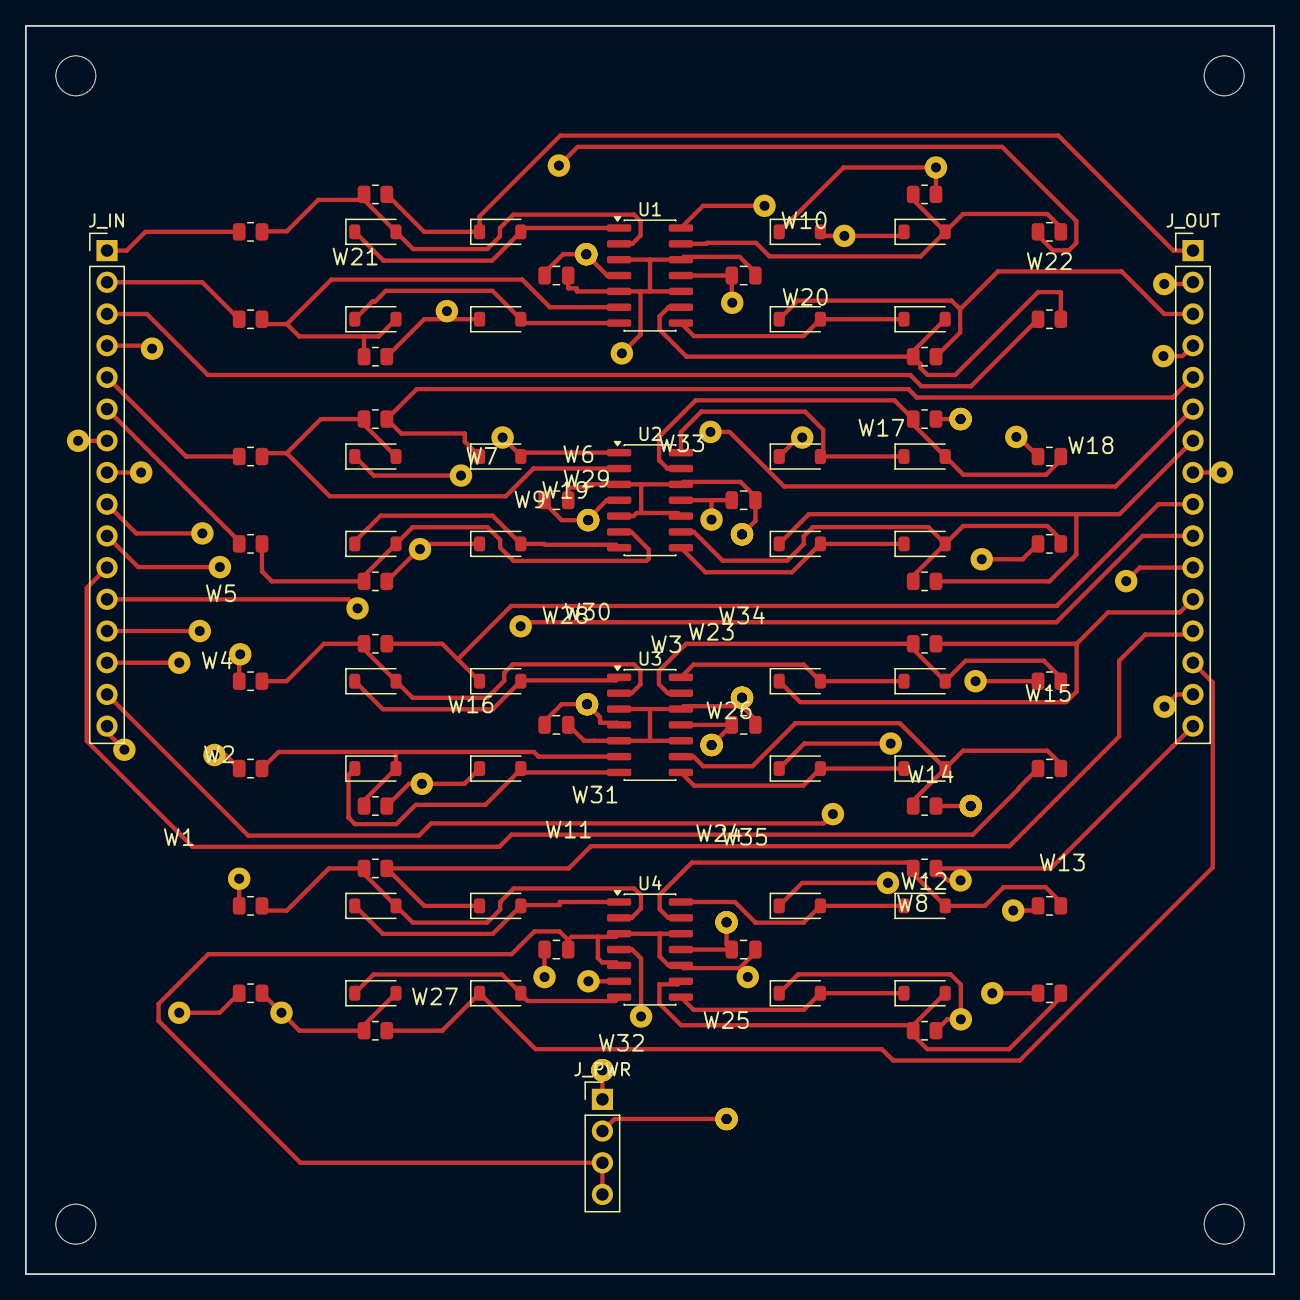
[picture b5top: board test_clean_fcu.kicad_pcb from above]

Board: 2 copper layers, 100.0 x 100.0 mm, 118 parts (0 on the bottom side), 67 nets.

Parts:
C_1_NEG, C_1_POS, C_2_NEG, C_2_POS, C_3_NEG, C_3_POS, C_4_NEG, C_4_POS: 100n; C_0805_2012Metric
D_FB_0, D_FB_1, D_FB_2, D_FB_3, D_FB_4, D_FB_5, D_FB_6, D_FB_7, D_FB_8, D_FB_9, D_FB_10, D_FB_11, D_FB_12, D_FB_13, D_FB_14, D_FB_15: 1N4148; D_SOD-123
D_OUT_0, D_OUT_1, D_OUT_2, D_OUT_3, D_OUT_4, D_OUT_5, D_OUT_6, D_OUT_7, D_OUT_8, D_OUT_9, D_OUT_10, D_OUT_11, D_OUT_12, D_OUT_13, D_OUT_14, D_OUT_15: 1N4148; D_SOD-123
J_IN: V_SUM_IN; PinHeader_1x16_P2.54mm_Vertical
J_OUT: ACT_OUT; PinHeader_1x16_P2.54mm_Vertical
J_PWR: POWER; PinHeader_1x04_P2.54mm_Vertical
MH1, MH2, MH3, MH4: MountingHole_3.2mm_M3
R_FB_0, R_FB_1, R_FB_2, R_FB_3, R_FB_4, R_FB_5, R_FB_6, R_FB_7, R_FB_8, R_FB_9, R_FB_10, R_FB_11, R_FB_12, R_FB_13, R_FB_14, R_FB_15: 10k; R_0805_2012Metric
R_IN_0, R_IN_1, R_IN_2, R_IN_3, R_IN_4, R_IN_5, R_IN_6, R_IN_7, R_IN_8, R_IN_9, R_IN_10, R_IN_11, R_IN_12, R_IN_13, R_IN_14, R_IN_15: 10k; R_0805_2012Metric
U1, U2, U3, U4: TL074; SOIC-14_3.9x8.7mm_P1.27mm
W1, W2, W3, W4, W5, W6, W7, W8, W9, W10, W11, W12, W13, W14, W15, W16, W17, W18, W19, W20, W21, W22, W23, W24, W25, W26, W27, W28, W29, W30, W31, W32, W33, W34, W35: JUMPER

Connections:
+12V: C_1_POS.1, C_2_POS.1, C_3_POS.1, C_4_POS.1, J_PWR.1, U1.4, U2.4, U3.4, U4.4, W28.1, W29.1, W30.1, W31.1, W32.1
-12V: C_1_NEG.1, C_2_NEG.1, C_3_NEG.1, C_4_NEG.1, J_PWR.2, U1.11, U2.11, U3.11, U4.11, W23.1, W24.1, W25.1, W26.1
ACT_0: D_OUT_0.1, J_OUT.1, R_FB_0.2
ACT_1: D_OUT_1.1, J_OUT.2, R_FB_1.2, W20.1
ACT_2: D_OUT_2.1, J_OUT.3, R_FB_2.2
ACT_3: D_OUT_3.1, J_OUT.4, R_FB_3.2, W22.1
ACT_4: D_OUT_4.1, J_OUT.5, R_FB_4.2
ACT_5: D_OUT_5.1, J_OUT.6, R_FB_5.2, W19.1
ACT_6: D_OUT_6.1, J_OUT.7, R_FB_6.2
ACT_7: D_OUT_7.1, J_OUT.8, R_FB_7.2, W17.1, W18.1
ACT_8: D_OUT_8.1, J_OUT.9, R_FB_8.2
ACT_9: D_OUT_9.1, J_OUT.10, R_FB_9.2, W16.1
ACT_10: D_OUT_10.1, J_OUT.11, R_FB_10.2, W14.1, W15.1
ACT_11: D_OUT_11.1, J_OUT.12, R_FB_11.2
ACT_12: D_OUT_12.1, J_OUT.13, R_FB_12.2
ACT_13: D_OUT_13.1, J_OUT.14, R_FB_13.2
ACT_14: D_OUT_14.1, J_OUT.15, R_FB_14.2, W13.1
ACT_15: D_OUT_15.1, J_OUT.16, R_FB_15.2, W12.1
GND: C_1_NEG.2, C_1_POS.2, C_2_NEG.2, C_2_POS.2, C_3_NEG.2, C_3_POS.2, C_4_NEG.2, C_4_POS.2, J_PWR.3, J_PWR.4, U1.3, U1.5, U1.10, U1.12, U2.3, U2.5, U2.10, U2.12, U3.3, U3.5, U3.10, U3.12, U4.3, U4.5, U4.10, U4.12, W33.1, W34.1, W35.1
INV_IN_0: D_FB_0.2, R_FB_0.1, R_IN_0.2, U1.2
INV_IN_1: D_FB_1.2, R_FB_1.1, R_IN_1.2, U1.6
INV_IN_2: D_FB_2.2, R_FB_2.1, R_IN_2.2, U1.9
INV_IN_3: D_FB_3.2, R_FB_3.1, R_IN_3.2, U1.13
INV_IN_4: D_FB_4.2, R_FB_4.1, R_IN_4.2, U2.2
INV_IN_5: D_FB_5.2, R_FB_5.1, R_IN_5.2, U2.6
INV_IN_6: D_FB_6.2, R_FB_6.1, R_IN_6.2, U2.9
INV_IN_7: D_FB_7.2, R_FB_7.1, R_IN_7.2, U2.13
INV_IN_8: D_FB_8.2, R_FB_8.1, R_IN_8.2, U3.2
INV_IN_9: D_FB_9.2, R_FB_9.1, R_IN_9.2, U3.6
INV_IN_10: D_FB_10.2, R_FB_10.1, R_IN_10.2, U3.9
INV_IN_11: D_FB_11.2, R_FB_11.1, R_IN_11.2, U3.13
INV_IN_12: D_FB_12.2, R_FB_12.1, R_IN_12.2, U4.2
INV_IN_13: D_FB_13.2, R_FB_13.1, R_IN_13.2, U4.6, W27.1
INV_IN_14: D_FB_14.2, R_FB_14.1, R_IN_14.2, U4.9
INV_IN_15: D_FB_15.2, R_FB_15.1, R_IN_15.2, U4.13
OP_OUT_0: D_FB_0.1, D_OUT_0.2, U1.1
OP_OUT_1: D_FB_1.1, D_OUT_1.2, U1.7
OP_OUT_2: D_FB_2.1, D_OUT_2.2, U1.8
OP_OUT_3: D_FB_3.1, D_OUT_3.2, U1.14, W10.1
OP_OUT_4: D_FB_4.1, D_OUT_4.2, U2.1, W7.1
OP_OUT_5: D_FB_5.1, D_OUT_5.2, U2.7
OP_OUT_6: D_FB_6.1, D_OUT_6.2, U2.8
OP_OUT_7: D_FB_7.1, D_OUT_7.2, U2.14
OP_OUT_8: D_FB_8.1, D_OUT_8.2, U3.1
OP_OUT_9: D_FB_9.1, D_OUT_9.2, U3.7
OP_OUT_10: D_FB_10.1, D_OUT_10.2, U3.8
OP_OUT_11: D_FB_11.1, D_OUT_11.2, U3.14
OP_OUT_12: D_FB_12.1, D_OUT_12.2, U4.1
OP_OUT_13: D_FB_13.1, D_OUT_13.2, U4.7
OP_OUT_14: D_FB_14.1, D_OUT_14.2, U4.8
OP_OUT_15: D_FB_15.1, D_OUT_15.2, U4.14
V_SUM_0: J_IN.1, R_IN_0.1
V_SUM_1: J_IN.2, R_IN_1.1
V_SUM_2: J_IN.3, R_IN_2.1
V_SUM_3: J_IN.4, R_IN_3.1, W21.1
V_SUM_4: J_IN.5, R_IN_4.1
V_SUM_5: J_IN.6, R_IN_5.1
V_SUM_6: J_IN.7, R_IN_6.1, W9.1
V_SUM_7: J_IN.8, R_IN_7.1, W6.1
V_SUM_8: J_IN.9, R_IN_8.1, W5.1
V_SUM_9: J_IN.10, R_IN_9.1, W4.1
V_SUM_10: J_IN.11, R_IN_10.1
V_SUM_11: J_IN.12, R_IN_11.1, W3.1
V_SUM_12: J_IN.13, R_IN_12.1, W2.1
V_SUM_13: J_IN.14, R_IN_13.1, W1.1
V_SUM_14: J_IN.15, R_IN_14.1, W8.1
V_SUM_15: J_IN.16, R_IN_15.1, W11.1
